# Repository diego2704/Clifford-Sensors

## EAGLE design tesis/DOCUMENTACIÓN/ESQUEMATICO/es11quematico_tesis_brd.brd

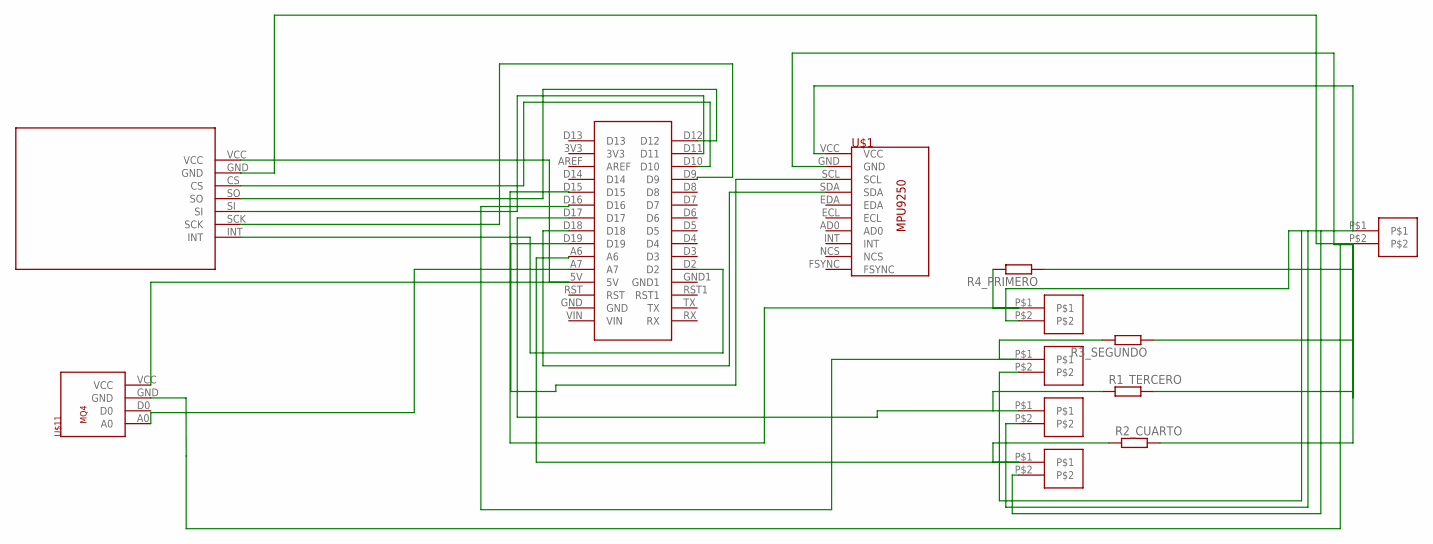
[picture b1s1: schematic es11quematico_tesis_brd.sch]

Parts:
ALIMENTACION: FSR402
CUARTO_FSR: FSR402
PRIMER_FSR: FSR402
R1_TERCERO, R2_CUARTO, R3_SEGUNDO, R4_PRIMERO: R-EU_0613/5V; P0613V
SEGUNDO_FSR: FSR402
TERCER_FSR: FSR402
U$1: MPU9250
U$2: ARDUINO-NANO
U$8: MCP2515
U$11: MQ4

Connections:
unnamed: ALIMENTACION.P$1, CUARTO_FSR.P$2, PRIMER_FSR.P$2, SEGUNDO_FSR.P$2, TERCER_FSR.P$2, U$1.VCC
unnamed: U$2.D10, U$8.CS
unnamed: ALIMENTACION.P$2, R1_TERCERO.2, R2_CUARTO.2, R3_SEGUNDO.1, R4_PRIMERO.1, U$1.GND, U$8.GND, U$11.GND
unnamed: U$2.D12, U$8.SO
unnamed: U$2.D11, U$8.SI
unnamed: U$2.D9, U$8.SCK
unnamed: U$2.D2, U$8.INT
unnamed: PRIMER_FSR.P$1, R4_PRIMERO.2, U$2.D15
unnamed: U$2.A7, U$11.A0
unnamed: U$1.SCL, U$2.D19
unnamed: U$1.SDA, U$2.D18
unnamed: CUARTO_FSR.P$1, R2_CUARTO.1, U$2.A6
unnamed: R1_TERCERO.1, TERCER_FSR.P$1, U$2.D17
unnamed: R3_SEGUNDO.2, SEGUNDO_FSR.P$1, U$2.D16
unnamed: U$2.5V, U$8.VCC, U$11.VCC

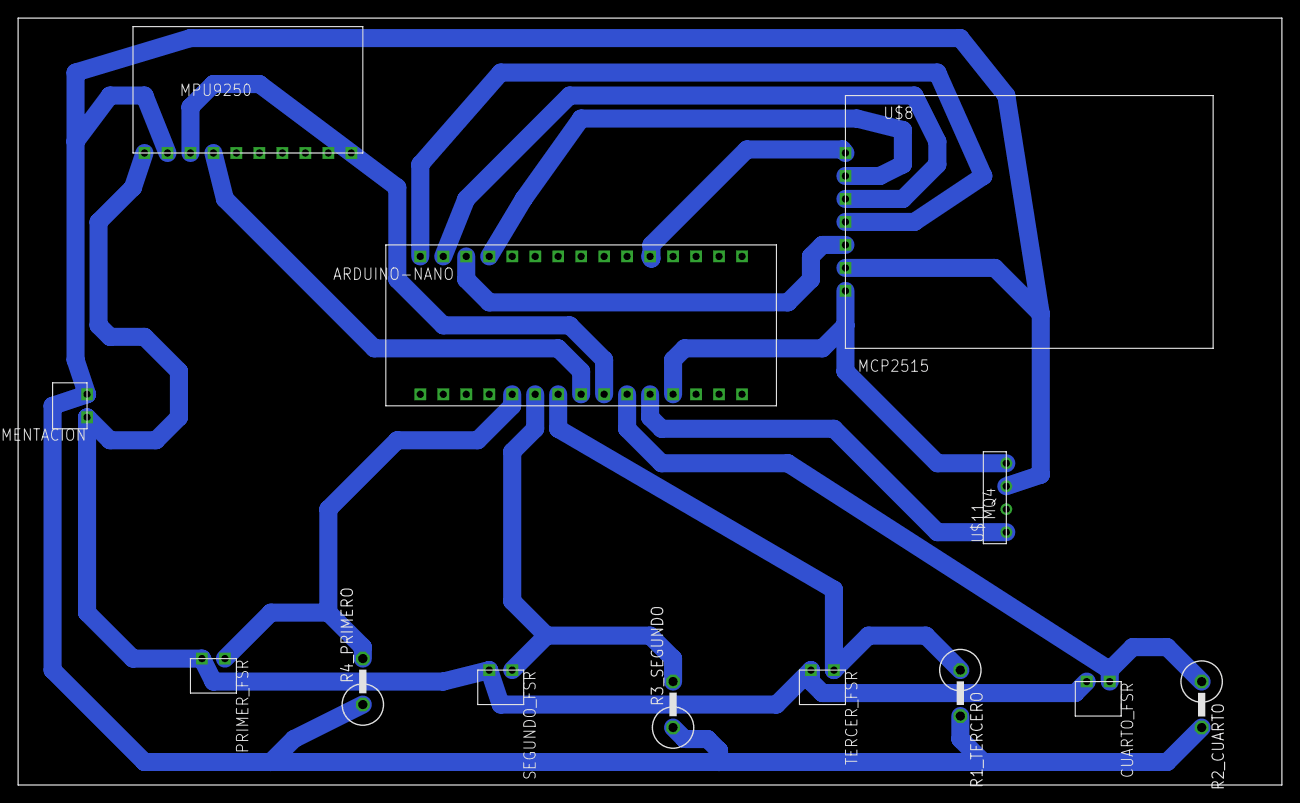
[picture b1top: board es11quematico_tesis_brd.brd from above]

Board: 2 copper layers, 139.7 x 84.8 mm, 13 parts (0 on the bottom side), 15 nets.

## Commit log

2024-09-24 Create Objetivo_general
